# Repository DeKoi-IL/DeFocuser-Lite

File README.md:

# DeFocuser-Lite
An open source DIY focus motor with automatic range calibration.

This focuser uses the same motor used by ZWO in the older EAF models (Non pro models)
The 3d models are also modelled based on ZWO's front plate so whatever focuser the eaf is compatible with, this is also compatible.
Powered by USB C 5V.
Includes a single button for manual focusing (each press changes direction).

## 3D Models

There are multiple versions for models.
You can get the motor ZWO used in their older models (described below, imaged above)
Or you could use a basic BYJ motor with a simple modification (How to modify: https://www.youtube.com/watch?v=kCoWSqSAGug)
Its great for lenses with suitable reduction!

Or you could retrofit the motor and front plate of the really old 12V ZWO focuser

All versions can be found in the 3d models folder

## App
Each app instance owns one focuser (one COM port) and funnels commands from multiple ASCOM clients to that focus motor. Run one instance per focuser — e.g. a main scope and a piggybacked guide/lens defocuser.

The hub owns all configuration, including which focuser ASCOM clients talk to: the driver has no setup dialog of its own, and pressing Setup in NINA/SGP just brings the hub forward. With a single focuser there is nothing to configure — the first hub to connect claims the ASCOM slot. Running several, click **Use this hub** in the Connection panel of the one you want ASCOM to drive.
The app has many extra controls not possible to implement in control software like nina, sgp etc...

## Disclaimer
This is NOT a beginner friendly project, since its all SMD components.
But this also is not a hard SMD project, just need the right tools.
Mainly a hot plat and\or hot air gun.
This is one of my first SMD projects, and im positive this has a LOT of room for improvement.
Please do feel free to reach out for contribution!

## BOM
For the motor you need to search for this motor: 35YF22GN120R-TF0
I bought it from this Ali Express seller (cheapest i found), but feel free to try and source it yourself:
https://he.aliexpress.com/item/1005004214871047.html

Technically, this should work with any 2 phase 4 wire stepper motor (as long as it doesn't draw too much current).
You'd just need to redesign the 3d model to fit your motor.

I've actually tested on a Nema17 39mm motor, and it seems to work fine, albeit low torque obviously.

The rest of the components are in the kicad folder BOM file.
*note: In the kicad project some components have LCSC part numbers, and some dont.
This is due to me using components i already had, and the rest i ordered from LCSC.
For the components without LCSC part number, you can just search by name in ali express for example.

## Hardware
The connection holes are meant to be fit with m3\4 heatset inserts (these: https://he.aliexpress.com/item/1005007481465353.html)
The PCB and backplate are held with m2 heatset inserts with m2 6mm screws.

## Software
The software is originally based on DarkSkyGeek's OAG focuser project.
A lot of the code has changed, most of it is different.
I'd like to  thank Julian for the inspiration 🙏

The current shipped app is a WPF rewrite (`Code/FocuserApp`) that replaces the older WinForms mediator (kept around as `Code/Focuser_App-Legacy/` for reference). It owns the serial connection to the focuser, exposes it to ASCOM clients via named pipes, and gives you a manual control UI on top.

This will allow multiple client connections to the focuser and give extra functionalities like:
- Auto\Manual limits calibration
- Manually settings position, max steps, reverse direction and more..
- Per-motor stall-detection sensitivity slider
- Speed selection (Fast / Normal / Slow)
- Live serial console (TX/RX, app events)

### Installing the app
The pre-built installer lives in the `Installer/` folder at the repo root:

```
Installer/DeKoi DeFocuser Lite Setup-<version>.exe
```

Run it. It installs both the ASCOM driver DLL (`ASCOM.DeKoi.DeFocuserLite.dll`) and the controller app (`ASCOM.DeKoi.DeFocuserApp.exe`), and registers the driver for COM under both 32-bit and 64-bit `regasm`. Requires ASCOM Platform 6.2 or later — the installer checks and bails out with a message if you don't have it.

If you want the prior WinForms version, the legacy installer source sits in `Code/Installer-Legacy/` and the legacy WinForms app in `Code/Focuser_App-Legacy/`. The standalone driver/installer that pre-dates all of this is preserved in `Code/Software-Legacy/`.

### Flashing the firmware
To flash the firmware on the ESP32, simply go to the arduino firmware folder, open the ino file in arduino IDE, compile and upload.
Make sure to have the ESP32 boards setup (Board manager) and set Xiao ESP32C3 (or S3)
And the following libraries:
- TMCStepper library by teemuatlut.
- EspSoftSerial by Dirk Kaar, Peter Lerup

## Building from source
The repo ships a one-shot build pipeline (`build.cmd` / `build.ps1`) that patches assembly versions, builds the ASCOM driver + the WPF controller, and compiles the Inno Setup installer in one go.

### Prerequisites
- Visual Studio 2019 / 2022 (Community / Pro / Enterprise / BuildTools — anything with MSBuild). The script auto-locates `MSBuild.exe`.
- [Inno Setup 6](https://jrsoftware.org/isdl.php) — script auto-locates `ISCC.exe`.
- ASCOM Platform 6.2 or later (the driver references `ASCOM.Utilities`).
- For the firmware: Arduino IDE with ESP32 boards + the libraries listed above.

### Build commands
From a regular `cmd.exe` prompt:

```cmd
build.cmd 2.1.0
build.cmd 2.1.0 -OutputDir D:\Releases
build.cmd 2.1.0 -SkipBuild
build.cmd 2.1.0 -Configuration Debug
```

From PowerShell:

```powershell
.\build.ps1 -Version 2.1.0
.\build.ps1 -Version 2.1.0 -OutputDir D:\Releases
.\build.ps1 -Version 2.1.0 -SkipBuild
.\build.ps1 -Version 2.1.0 -Configuration Debug
```

What it does:
1. Patches `AssemblyVersion` + `AssemblyFileVersion` in `Code/FocuserApp/Properties/AssemblyInfo.cs` and `Code/ASCOM_Driver/Properties/AssemblyInfo.cs`.
2. Builds the ASCOM driver (`Release | AnyCPU`).
3. Builds the WPF app (`Release | x64`).
4. Compiles `Code/FocuserApp/Installer/Setup.iss` with `ISCC`, injecting `/DMyAppVersion=<version>`.
5. Drops the resulting `DeKoi DeFocuser Lite Setup-<version>.exe` into `Installer/` (or whatever you pass to `-OutputDir`).

The fonts used by the app are **Inter** (UI) and **JetBrains Mono** (numeric readouts). Both are free OFL fonts; install them system-wide for pixel-perfect rendering — fallback to system fonts otherwise.

## Automatic limits calibration
This is very motor and configuration specific.
Not every motor behaves the same since the TMC's way of detecting stalls is back EMF measurement, and your motor might not behave as well as mine with the same configurations.

The first place to tune is the **Stall sense** slider in the controller app's Focuser Settings card — it scrubs the TMC's `SGTHRS` register from `128` (most sensitive) to `255` (least sensitive). The value persists to EEPROM, so you only set it once. Default is `211`.

If the slider alone doesn't get you where you want, there are a few firmware-side parameters you can tweak in `Code/Arduino_Firmware/Arduino_Firmware.ino`:

```
#define STALL_COUNT_THRESHOLD 2 // How many time should the stall interrupt be raised before we consider real stall
#define STALL_TIME_THRS 300     // In what time frame should these stalls be detected (in milliseconds)
#define STALL_GRACE_PERIOD 1000 // When starting motor, there are many false detections, how long should we ignore stall detections (in milliseconds)
```

Lets say the motor hits a hard physical limit but motor still makes noise trying to move (IE stall wasn't detected),
Try changing one of the following one by one (changing multiple parameters might make fine tuning harder):
- **Stall sense slider** = Start by sliding it toward the "Most sensitive" end, see if the stall is detected sooner.
- `STALL_TIME_THRS` = Increase this to allow slow stall detections to accumulate.
- `STALL_COUNT_THRESHOLD` = You could reduce this, but i suggest not doing that since that might increase false detections.

If this doesn't work, set `DEBUG` to `1` and watch the stall logs in the app's console — you'll see how often (or whether) stalls get detected. If they don't fire at all, or fire too slowly, slide stall sense further toward "Most sensitive".

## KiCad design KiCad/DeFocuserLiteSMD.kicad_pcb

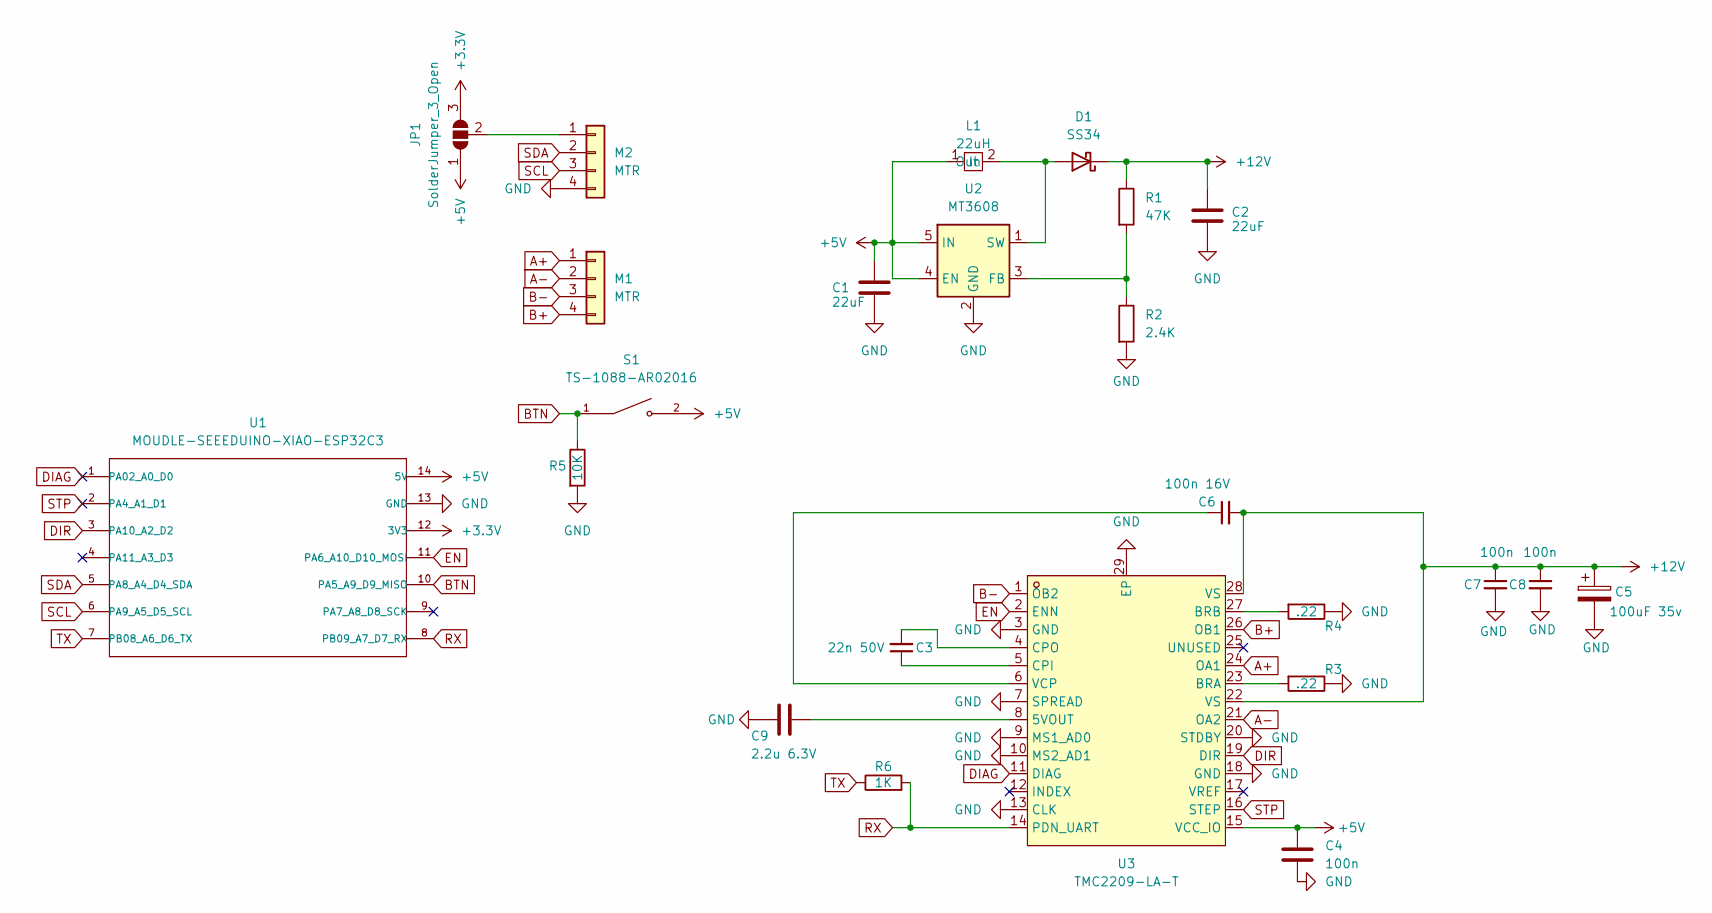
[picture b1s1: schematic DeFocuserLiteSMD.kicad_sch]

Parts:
C1, C2: 22uF; C_1812_4532Metric; LCSC Part C5348165
C3: 22n 50V; C_0805_2012Metric; LCSC Part C2175869
C4: 100n; C_1206_3216Metric; LCSC Part C2180991
C5: 100uF 35v; CP_Elec_6.3x7.7; LCSC Part C2836442
C6: 100n 16V; R_0805_2012Metric; LCSC Part C2170367
C7, C8: 100n; C_0805_2012Metric; LCSC Part C2170367
C9: 2.2u 6.3V; C_0805_2012Metric; LCSC Part C520034
D1: SS34; D_SMA-SMB_Universal_Handsoldering; LCSC Part C908680
JP1: SolderJumper_3_Open; SolderJumper-3_P1.3mm_Open_RoundedPad1.0x1.5mm_NumberLabels
L1: 22uH; Inductor_CDRH104R; LCSC Part C87002
M1, M2: MTR; JST_XH_B4B-XH-A_1x04_P2.50mm_Vertical
R1: 47K; R_1206_3216Metric_Pad1.30x1.75mm_HandSolder; LCSC Part C2933708
R2: 2.4K; R_1206_3216Metric_Pad1.30x1.75mm_HandSolder; LCSC Part C2907446
R3, R4: .22; R_1210_3225Metric; LCSC Part C137099
R5: 10K; R_1206_3216Metric; LCSC Part C17902
R6: 1K; R_1206_3216Metric; LCSC Part C2907440
S1: TS-1088-AR02016; SW_TS-1088-AR02016; PARTREV N/A; LCSC Part C720477
U1: MOUDLE-SEEEDUINO-XIAO-ESP32C3; XIAO-ESP32C3-SMD
U2: MT3608; SOT-23-6; LCSC Part C84817
U3: TMC2209-LA-T; QFN-28_L5.0-W5.0-P0.50-BL-EP; LCSC Part C2150710

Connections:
+3.3V: JP1.3 (B), U1.12 (3V3)
+5V: C1.1, C4.1, JP1.1 (A), L1.1 (In), S1.2, U1.14 (5V), U2.4 (EN), U2.5 (IN), U3.15 (VCC_IO)
+12V: C2.1, C5.1, C6.2, C7.1, C8.1, D1.1 (K), R1.1, U3.22 (VS), U3.28 (VS)
A+: M1.1, U3.24 (OA1); also elsewhere on the board
A-: M1.2, U3.21 (OA2); also elsewhere on the board
B+: M1.4, U3.26 (OB1); also elsewhere on the board
B-: M1.3, U3.1 (OB2); also elsewhere on the board
BTN: R5.1, S1.1, U1.10 (PA5_A9_D9_MISO)
DIAG: U1.1 (PA02_A0_D0), U3.11 (DIAG)
DIR: U1.3 (PA10_A2_D2), U3.19 (DIR)
EN: U1.11 (PA6_A10_D10_MOSI), U3.2 (ENN)
GND: C1.2, C2.2, C4.2, C5.2, C7.2, C8.2, C9.2, M2.4, R2.2, R3.1, R4.1, R5.2, U1.13 (GND), U2.2 (GND), U3.3 (GND), U3.7 (SPREAD), U3.9 (MS1_AD0), U3.10 (MS2_AD1), U3.13 (CLK), U3.18 (GND), U3.20 (STDBY), U3.29 (EP); also elsewhere on the board
unnamed: D1.2 (A), L1.2 (Out), U2.1 (SW)
unnamed 13: JP1.2 (C), M2.1; also elsewhere on the board
unnamed: R1.2, R2.1, U2.3 (FB)
unnamed: C9.1, U3.8 (5VOUT)
unnamed: R3.2, U3.23 (BRA)
unnamed: R4.2, U3.27 (BRB)
unnamed: C3.1, U3.5 (CPI)
unnamed: C3.2, U3.4 (CPO)
unnamed: C6.1, U3.6 (VCP)
RX: R6.2, U1.8 (PB09_A7_D7_RX), U3.14 (PDN_UART)
SCL: M2.3, U1.6 (PA9_A5_D5_SCL); also elsewhere on the board
SDA: M2.2, U1.5 (PA8_A4_D4_SDA); also elsewhere on the board
STP: U1.2 (PA4_A1_D1), U3.16 (STEP)
TX: R6.1, U1.7 (PB08_A6_D6_TX)

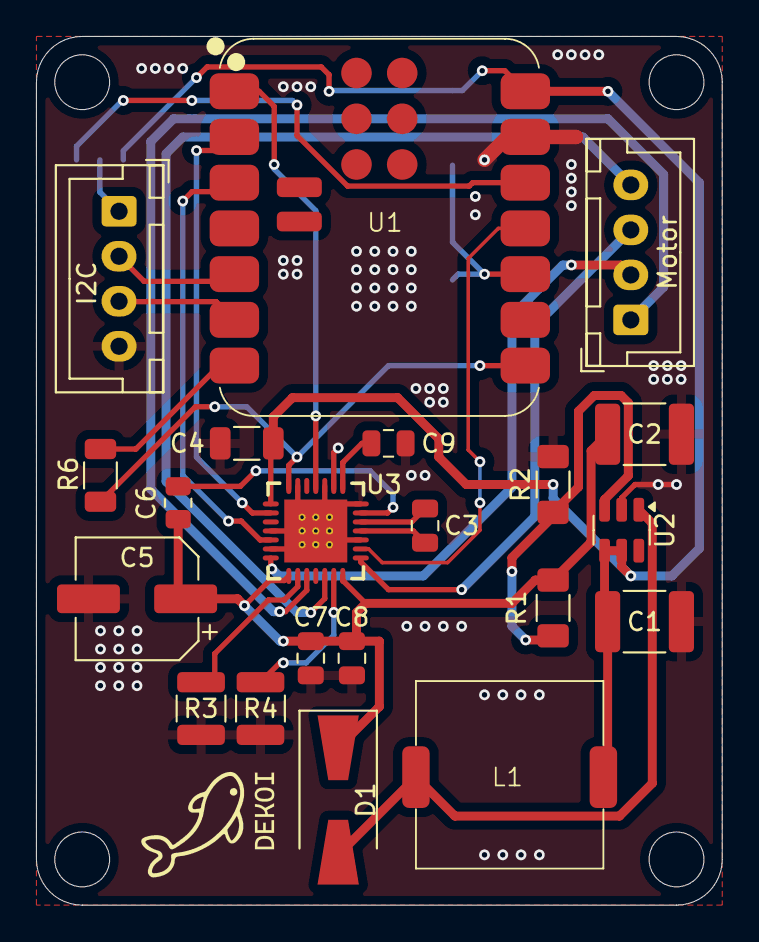
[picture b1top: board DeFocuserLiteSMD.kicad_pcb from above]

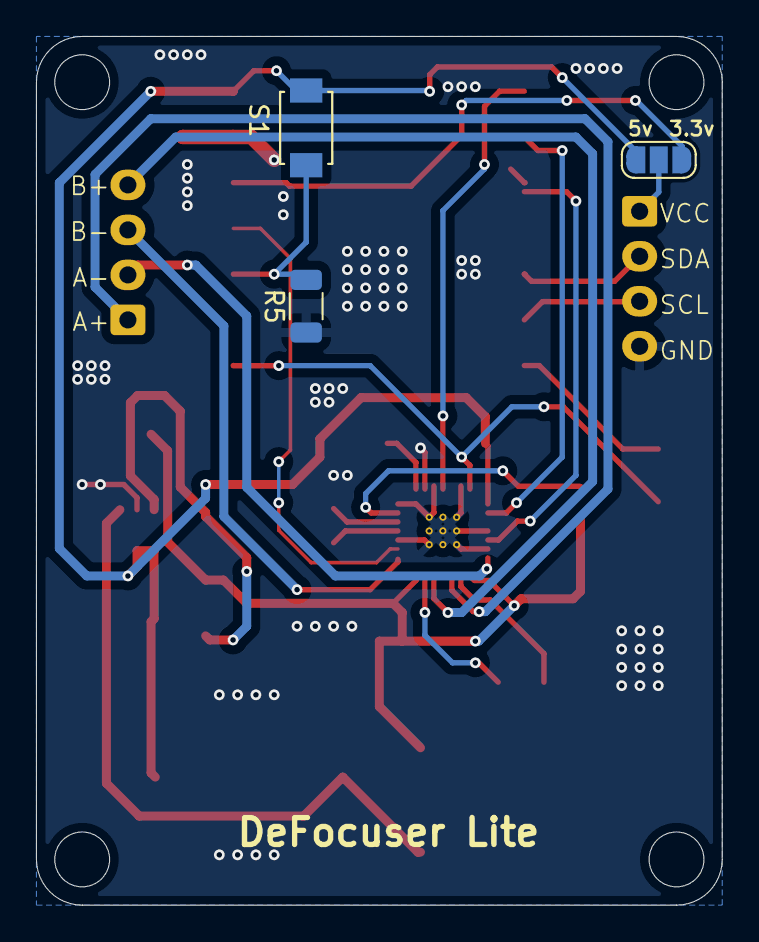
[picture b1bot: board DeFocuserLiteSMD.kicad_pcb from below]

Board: 2 copper layers, 38.1 x 48.3 mm, 24 parts (3 on the bottom side), 26 nets.

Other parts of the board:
I2C: MTR; JST_XH_B4B-XH-A_1x04_P2.50mm_Vertical
Motor: MTR; JST_XH_B4B-XH-A_1x04_P2.50mm_Vertical

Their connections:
A+: Motor.1; also elsewhere on the board
A-: Motor.2; also elsewhere on the board
B+: Motor.4; also elsewhere on the board
B-: Motor.3; also elsewhere on the board
GND: I2C.4; also elsewhere on the board
unnamed 13: I2C.1; also elsewhere on the board
SCL: I2C.3; also elsewhere on the board
SDA: I2C.2; also elsewhere on the board

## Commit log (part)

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2025-12-08 Part number update
2025-12-09 Fixed resistor value + reexported BOM
2025-12-09 Added lcsc part numbers with in stock components
2025-12-21 Fixes
2025-12-21 Delay only in debug mode
2026-03-03 Remove old image
2026-03-03 Trying V2 with better pcb layout to expose I2C, and new driver with standalone app integrated as a mediator
2026-03-03 New image
2026-03-03 New builds, now works
2026-03-03 Cleanup and fixes
2026-03-03 Multi client ready
2026-03-03 New models
2026-03-03 Exported f3d file
2026-03-04 New gerbers and BOM
2026-03-04 Removed unused var
2026-03-05 Cleanup
2026-04-29 New App!
2026-04-29 Correct version in console log
2026-05-06 Driver pointed at legacy app
2026-05-06 Full run current
2026-05-16 Embedd ESPtool + Github release check for updates + Auto install and firmware flashing
2026-05-16 Fixes and improvements
2026-05-16 Removed build artifacts, updated build script to auto delete
2026-05-16 Small bug fix
2026-05-21 Stall settings in settings popup
2026-06-11 Support for multiple instances for multiple single pc focusers
